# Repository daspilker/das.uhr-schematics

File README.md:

DAS.UHR Schematics
==================

This repository contains the schematics and PCB design files for the DAS.UHR word clock.

These files have been created with the [EAGLE](http://www.cadsoftusa.com/) PCB software.

The PCB design meets the specifications of [OSH Park](http://oshpark.com/) community PCB order.

Bill Of Materials
-----------------

ICs
* **IC1** MCP1700 voltage regulator 3.3V 250mA TO-92-3 (Digi-Key MCP1700-3302E/TO-ND)
* **IC2** ATMEGA88PA 28-DIP (Digi-Key ATMEGA88PA-PU-ND)
* **IC3** 74HC4017 counter 16-DIP (Digi-Key 1026-M74HC4017B1R-CHP)
* **IC4-IC6** quad-MOSFET 14-DIP (Digi-Key TC4468CPD-ND)
* **IC7** PWM LED driver 28-DIP (Digi-Key 296-17732-5-ND)
* **IC8** DCF-77 receiver (Pollin 810 054)
* **IC9** real-time clock 8-DIP (Digi-Key DS1307+-ND)
* **CON2** serial Bluetooth transceiver module JY-MCU BT_BOARD V1.2 (eBay)

Capactitors
* **C1, C2** ceramic 1µF 50V (Digi-Key 490-5375-ND)
* **C3-C9** ceramic 100nF 50V (Digi-Key 490-3811-ND)
* **C10** electrolytic 100µF 10V (Digi-Key P5123-ND)

Resistors
* **R1, R4-R6** 10kΩ (Digi-Key 10KQBK-ND)
* **R2** 1kΩ (Digi-Key 1.0KQBK-ND)
* **R3** 330Ω (Digi-Key 330QBK-ND)
* **R7** trimmer 5kΩ (Digi-Key CT6EP502-ND)
* **R8+R9** 2.2kΩ (Digi-Key 2.2KQBK-ND)

Other
* **Q1** crystal 32.768 kHz 12.5pF (Digi-Key 300-8303-ND)
* **LED1** LED 3mm (Digi-Key 754-1211-ND)
* **T1** ambient light sensor (Digi-Key 751-1059-ND)
* micro-USB power supply 5V 500mA (Digi-Key 454-1496-ND)
* Nichia Superflux LED white 10lm 100° NSPWR70CSS (LUMITRONIX 11011)

Sockets and Connectors
* **CON1** micro-USB A/B receptacle SMD 90° (Digi-Key H11635CT-ND)
* **CON2** female header 6-pos 2.54mm 90° (Digi-Key S5481-ND)
* **ISP1** header 6-pos 2.54mm (Digi-Key 609-3210-ND)
* **CON3, CON4** header 2.54mm 36-pos (Digi-Key S1011E-36-ND)
* **IC2, IC7** DIP socket 28-pos (Digi-Key A100210-ND)
* **IC3** DIP socket 16-pos (Digi-Key A100206-ND)
* **IC4-IC6** DIP socket 14-pos (Digi-Key A100205-ND)
* **IC8** female header 4-pos 2.54mm (Digi-Key S7037-ND)
* **IC9** DIP socket 8-pos (Digi-Key A100204-ND)

License
-------

Copyright 2012 Daniel A. Spilker

Licensed under the Apache License, Version 2.0 (the "License");
you may not use this file except in compliance with the License.
You may obtain a copy of the License at

    http://www.apache.org/licenses/LICENSE-2.0

Unless required by applicable law or agreed to in writing, software
distributed under the License is distributed on an "AS IS" BASIS,
WITHOUT WARRANTIES OR CONDITIONS OF ANY KIND, either express or implied.
See the License for the specific language governing permissions and
limitations under the License.

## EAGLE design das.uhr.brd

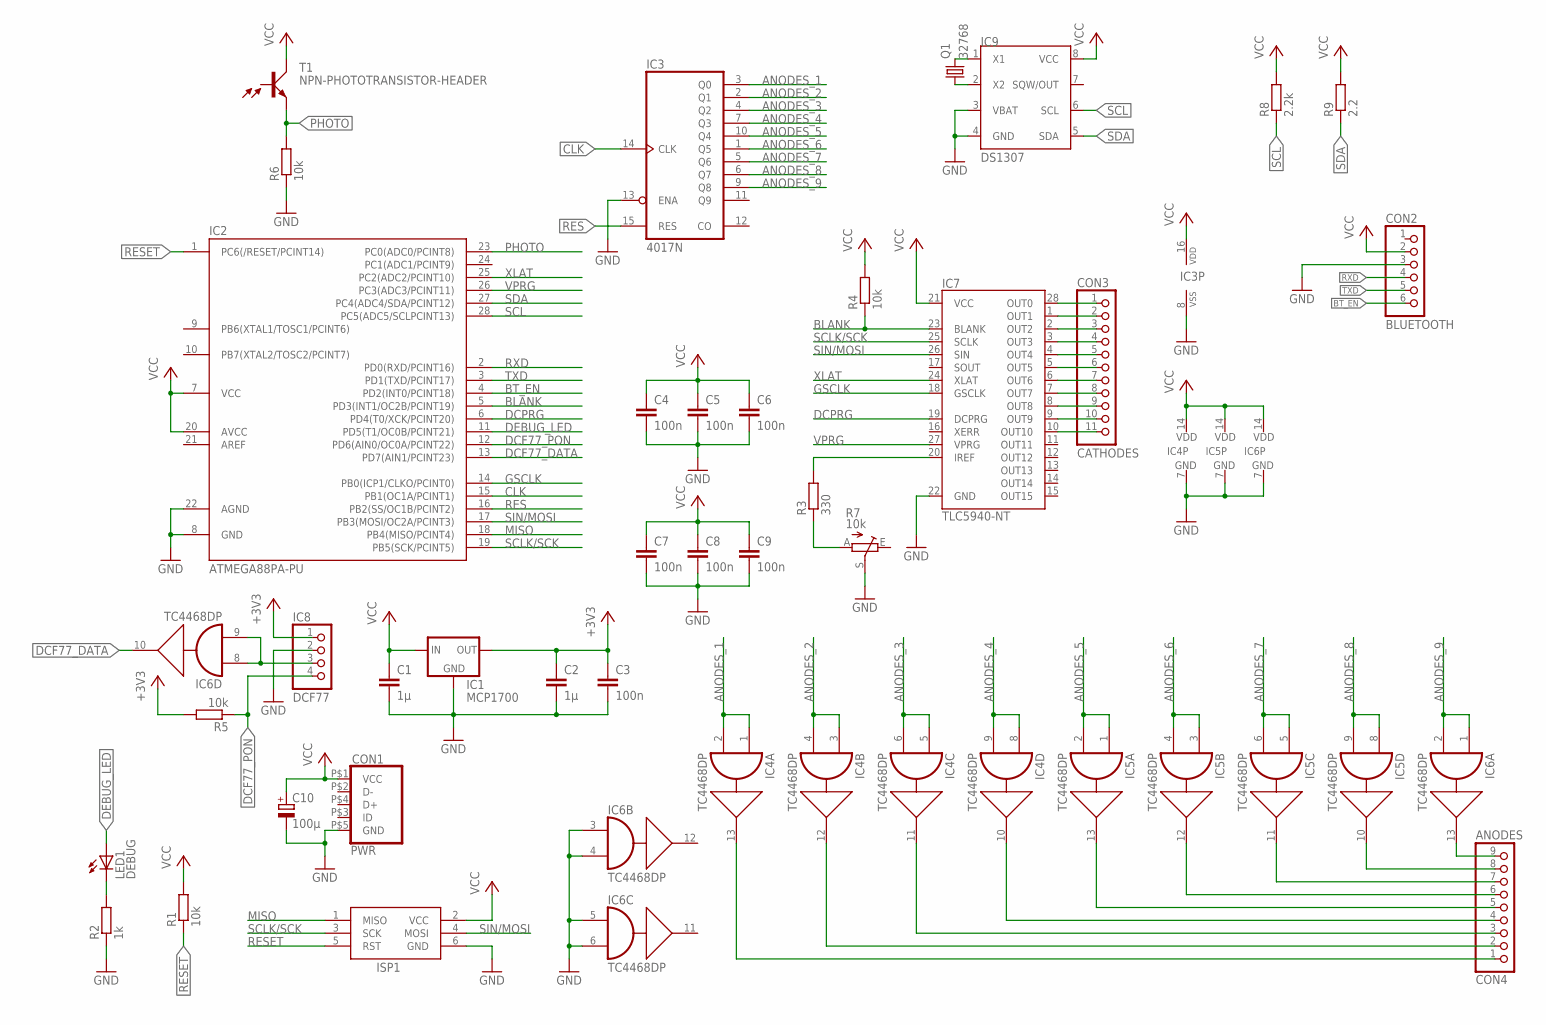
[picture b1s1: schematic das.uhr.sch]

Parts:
C1, C2: 1µ; C050-024X044
C3, C4, C5, C6, C7, C8, C9: 100n; C050-024X044
C10: 100µ; E2,5-5
CON1: PWR; HIROSE-ZX62-AB-5PA(11)
CON2: BLUETOOTH; 1X06
CON3: CATHODES; 1X11
CON4: ANODES; 1X09
IC1: MCP1700; TO92-INLINE
IC2: ATMEGA88PA-PU; DIL28-3
IC3: 4017N; DIL16
IC4, IC5, IC6: TC4468DP; DIL14
IC7: TLC5940-NT; DIL28-3
IC8: DCF77; 1X04
IC9: DS1307; DIL08
ISP1: AVRISP-6; AVRISP
LED1: DEBUG; LED3MM
Q1: 32768; TC26V
R1, R4, R5, R6: 10k; 0207/7
R2: 1k; 0207/7
R3: 330; 0207/7
R7: 10k; S63P
R8: 2.2k; 0207/7
R9: 2.2; 0207/7
T1: NPN-PHOTOTRANSISTOR-HEADER; 1X02-S

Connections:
+3V3: C2.1, C3.1, IC1.3 (OUT), IC8.1, R5.2
ANODES_1: IC3.3 (Q0), IC4.1 (A), IC4.2 (B)
ANODES_2: IC3.2 (Q1), IC4.3 (A), IC4.4 (B)
ANODES_3: IC3.4 (Q2), IC4.5 (A), IC4.6 (B)
ANODES_4: IC3.7 (Q3), IC4.8 (A), IC4.9 (B)
ANODES_5: IC3.10 (Q4), IC5.1 (A), IC5.2 (B)
ANODES_6: IC3.1 (Q5), IC5.3 (A), IC5.4 (B)
ANODES_7: IC3.5 (Q6), IC5.5 (A), IC5.6 (B)
ANODES_8: IC3.6 (Q7), IC5.8 (A), IC5.9 (B)
ANODES_9: IC3.9 (Q8), IC6.1 (A), IC6.2 (B)
BLANK: IC2.5 (PD3(INT1/OC2B/PCINT19)), IC7.23 (BLANK), R4.1
BT_EN: CON2.6, IC2.4 (PD2(INT0/PCINT18))
CLK: IC2.15 (PB1(OC1A/PCINT1)), IC3.14 (CLK)
DCF77_DATA: IC2.13 (PD7(AIN1/PCINT23)), IC6.10 (Y)
DCF77_PON: IC2.12 (PD6(AIN0/OC0A/PCINT22)), IC8.4, R5.1
DCPRG: IC2.6 (PD4(T0/XCK/PCINT20)), IC7.19 (DCPRG)
DEBUG_LED: IC2.11 (PD5(T1/OC0B/PCINT21)), LED1.A
GND: C1.2, C2.2, C3.2, C4.2, C5.2, C6.2, C7.2, C8.2, C9.2, C10.-, CON1.P$5 (GND), CON2.3, IC1.1 (GND), IC2.8 (GND), IC2.22 (AGND), IC3.8 (VSS), IC3.13 (ENA), IC4.7 (GND), IC5.7 (GND), IC6.3 (A), IC6.4 (B), IC6.5 (A), IC6.6 (B), IC6.7 (GND), IC7.22 (GND), IC8.2, IC9.3 (VBAT), IC9.4 (GND), ISP1.6 (GND), R2.1, R6.1, R7.S
GSCLK: IC2.14 (PB0(ICP1/CLKO/PCINT0)), IC7.18 (GSCLK)
MISO: IC2.18 (PB4(MISO/PCINT4)), ISP1.1 (MISO)
unnamed: LED1.K (C), R2.2
unnamed: CON3.1, IC7.28 (OUT0)
unnamed: CON3.2, IC7.1 (OUT1)
unnamed: CON3.3, IC7.2 (OUT2)
unnamed: CON3.4, IC7.3 (OUT3)
unnamed: CON3.5, IC7.4 (OUT4)
unnamed: CON3.6, IC7.5 (OUT5)
unnamed: CON3.7, IC7.6 (OUT6)
unnamed: CON3.8, IC7.7 (OUT7)
unnamed: CON3.9, IC7.8 (OUT8)
unnamed: CON3.10, IC7.9 (OUT9)
unnamed: CON3.11, IC7.10 (OUT10)
unnamed: IC7.20 (IREF), R3.2
unnamed: CON4.9, IC6.13 (Y)
unnamed: CON4.8, IC5.10 (Y)
unnamed: CON4.7, IC5.11 (Y)
unnamed: CON4.6, IC5.12 (Y)
unnamed: CON4.5, IC5.13 (Y)
unnamed: CON4.4, IC4.10 (Y)
unnamed: CON4.3, IC4.11 (Y)
unnamed: CON4.2, IC4.12 (Y)
unnamed: CON4.1, IC4.13 (Y)
unnamed: IC6.8 (A), IC6.9 (B), IC8.3
unnamed: R3.1, R7.A
unnamed: IC9.1 (X1), Q1.2
unnamed: IC9.2 (X2), Q1.1
PHOTO: IC2.23 (PC0(ADC0/PCINT8)), R6.2, T1.2 (E)
RES: IC2.16 (PB2(SS/OC1B/PCINT2)), IC3.15 (RES)
RESET: IC2.1 (PC6(/RESET/PCINT14)), ISP1.5 (RST), R1.1
RXD: CON2.4, IC2.2 (PD0(RXD/PCINT16))
SCL: IC2.28 (PC5(ADC5/SCLPCINT13)), IC9.6 (SCL), R8.1
SCLK/SCK: IC2.19 (PB5(SCK/PCINT5)), IC7.25 (SCLK), ISP1.3 (SCK)
SDA: IC2.27 (PC4(ADC4/SDA/PCINT12)), IC9.5 (SDA), R9.1
SIN/MOSI: IC2.17 (PB3(MOSI/OC2A/PCINT3)), IC7.26 (SIN), ISP1.4 (MOSI)
TXD: CON2.5, IC2.3 (PD1(TXD/PCINT17))
VCC: C1.1, C4.1, C5.1, C6.1, C7.1, C8.1, C9.1, C10.+, CON1.P$1 (VCC), CON2.2, IC1.2 (IN), IC2.7 (VCC), IC2.20 (AVCC), IC3.16 (VDD), IC4.14 (VDD), IC5.14 (VDD), IC6.14 (VDD), IC7.21 (VCC), IC9.8 (VCC), ISP1.2 (VCC), R1.2, R4.2, R8.2, R9.2, T1.1 (C)
VPRG: IC2.26 (PC3(ADC3/PCINT11)), IC7.27 (VPRG)
XLAT: IC2.25 (PC2(ADC2/PCINT10)), IC7.24 (XLAT)

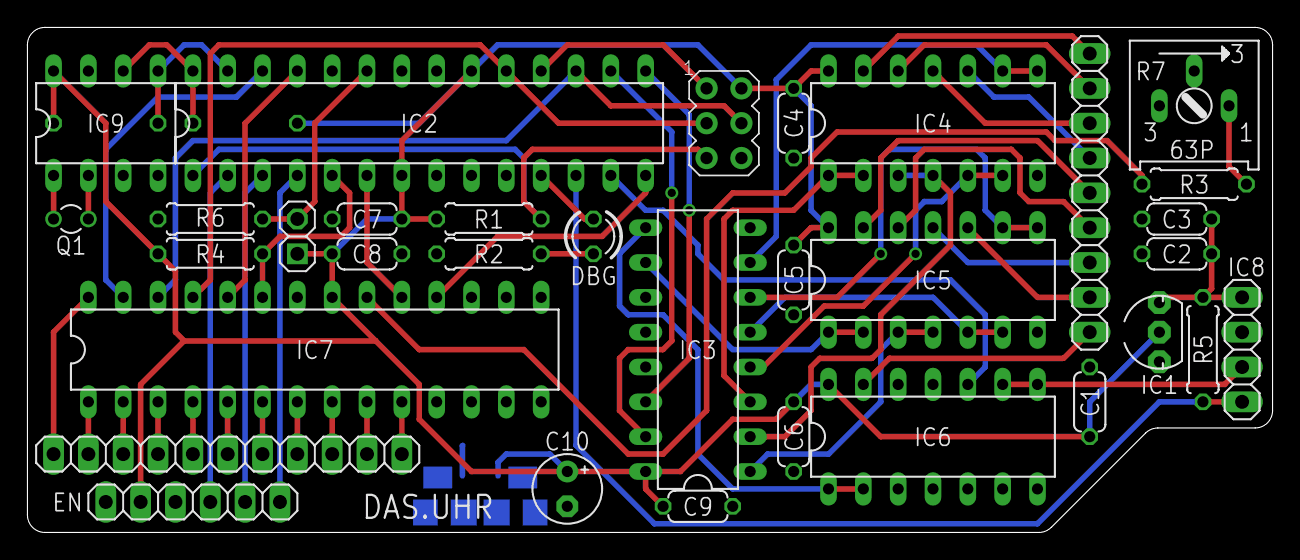
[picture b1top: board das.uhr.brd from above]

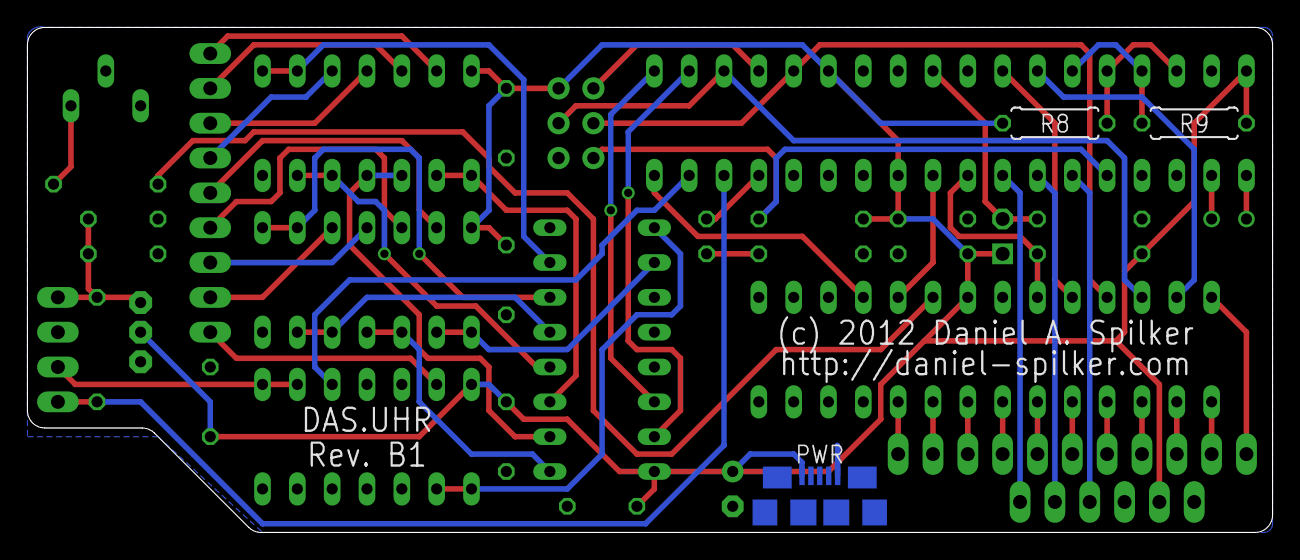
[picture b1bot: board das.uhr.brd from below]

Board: 2 copper layers, 90.8 x 36.8 mm, 36 parts (2 on the bottom side), 58 nets.

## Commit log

2013-07-28 Rev. B1
2013-07-29 added license and readme
2013-07-30 updated BOM
2013-07-30 removed duplicate parts from BOM

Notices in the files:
das.uhr.brd:
(c) 2012 Daniel A. Spilker
